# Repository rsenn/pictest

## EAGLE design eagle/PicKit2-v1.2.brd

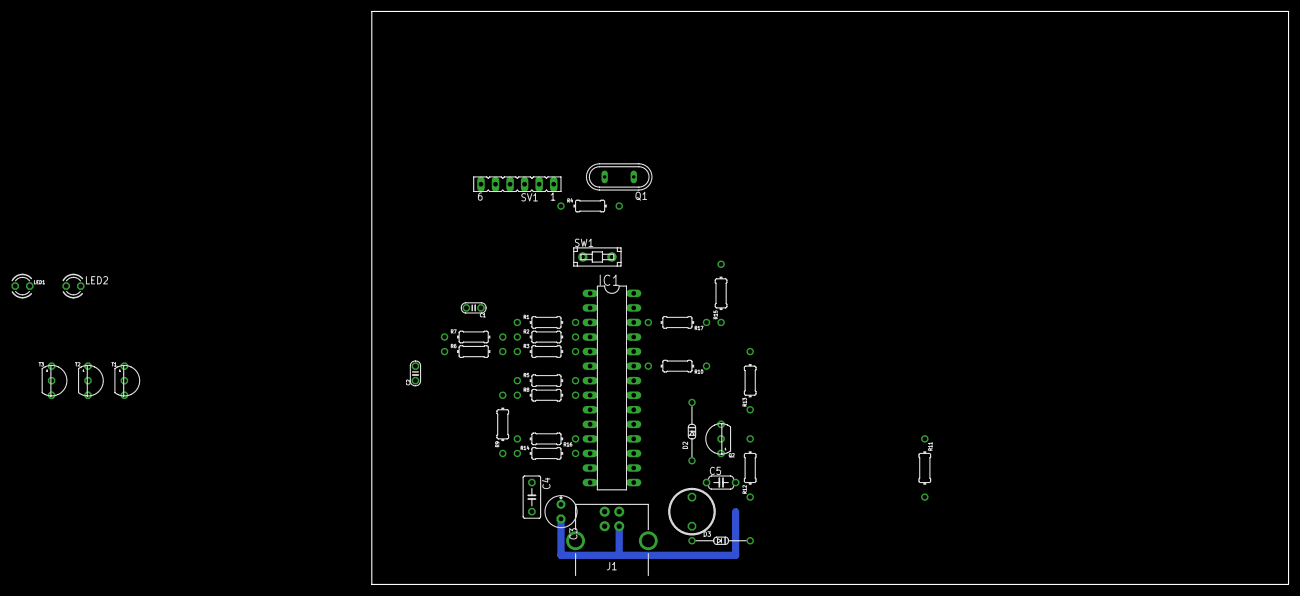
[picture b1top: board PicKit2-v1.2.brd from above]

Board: 2 copper layers, 160.0 x 100.0 mm, 36 parts (0 on the bottom side), 32 nets.

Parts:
C1, C2: 22p; C025-020X036
C3: 47 μF; E2,5-6E
C4: 0.47 μF; C050-030X075
C5: 0.1 μF; C050-024X044
D2: 1N5817-B; DO34Z10
D3: DO34-10
IC1: PIC18F2550_28DIP; DIL28-3
J1: USB-PRINT; USB-B-PRINT
L1: 680μH; L-8R
LED1: Red Busy; LED_3MM
LED2: Green Power; LED3MM
Q1: 20 MHz; QS
Q2: 2N3906; TO92
R1, R6, R7, R9: 4.7kΩ; 0204/10
R2, R3, R4, R13: 100Ω; 0204/10
R5, R10, R11: 10kΩ; 0204/10
R8: 2.7kΩ; 0204/10
R12: 100kΩ; 0204/10
R14: 1kΩ; 0204/10
R15, R16: 330Ω; 0204/10
R17: 22kΩ; 0204/10
SV1: FE06
SW1: PB-1P-1T; PB-1P1T
T1, T2, T3: 2N3904; TO92

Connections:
GND: C1.2, C2.2, C3.-, C4.2, C5.2, IC1.8, IC1.19, J1.GND, LED1.K, LED2.K, R6.1, R7.1, R8.2, SV1.3, SW1.2, T1.1, T2.1, T3.1
unnamed: C1.1, IC1.9, Q1.1
unnamed: C2.1, IC1.10, Q1.2
unnamed: IC1.3, R1.2
unnamed: IC1.4, R2.2
unnamed: IC1.5, R3.2
unnamed: IC1.6, R4.2
unnamed: IC1.7, R5.2
unnamed: D2.C, R1.1, SV1.2
unnamed: R2.1, R7.2, SV1.4
unnamed: R3.1, R6.2, SV1.5
unnamed: R4.1, SV1.6
unnamed: IC1.2, R8.1, R9.2
unnamed: IC1.23, R10.2
unnamed: R10.1, T1.2
unnamed: R11.2, T1.3
unnamed: Q2.2, R11.1, R12.2
unnamed: C3.+, D3.C, Q2.1, R9.1, R12.1
unnamed: IC1.12, R14.2
unnamed: R5.1, T2.2
unnamed: Q2.3, R13.1, SV1.1
unnamed: R13.2, T2.3
unnamed: R14.1, T3.2
unnamed: D3.A, L1.P$1, T3.3
unnamed: LED2.A, R15.2
unnamed: IC1.11, R16.1
unnamed: LED1.A, R16.2
unnamed: IC1.16, J1.D-
unnamed: IC1.15, J1.D+
unnamed: IC1.26, R17.2, SW1.1
VDD: C5.1, D2.A, IC1.20, J1.VBUS, L1.P$2, R15.1, R17.1
VUSB: C4.1, IC1.14

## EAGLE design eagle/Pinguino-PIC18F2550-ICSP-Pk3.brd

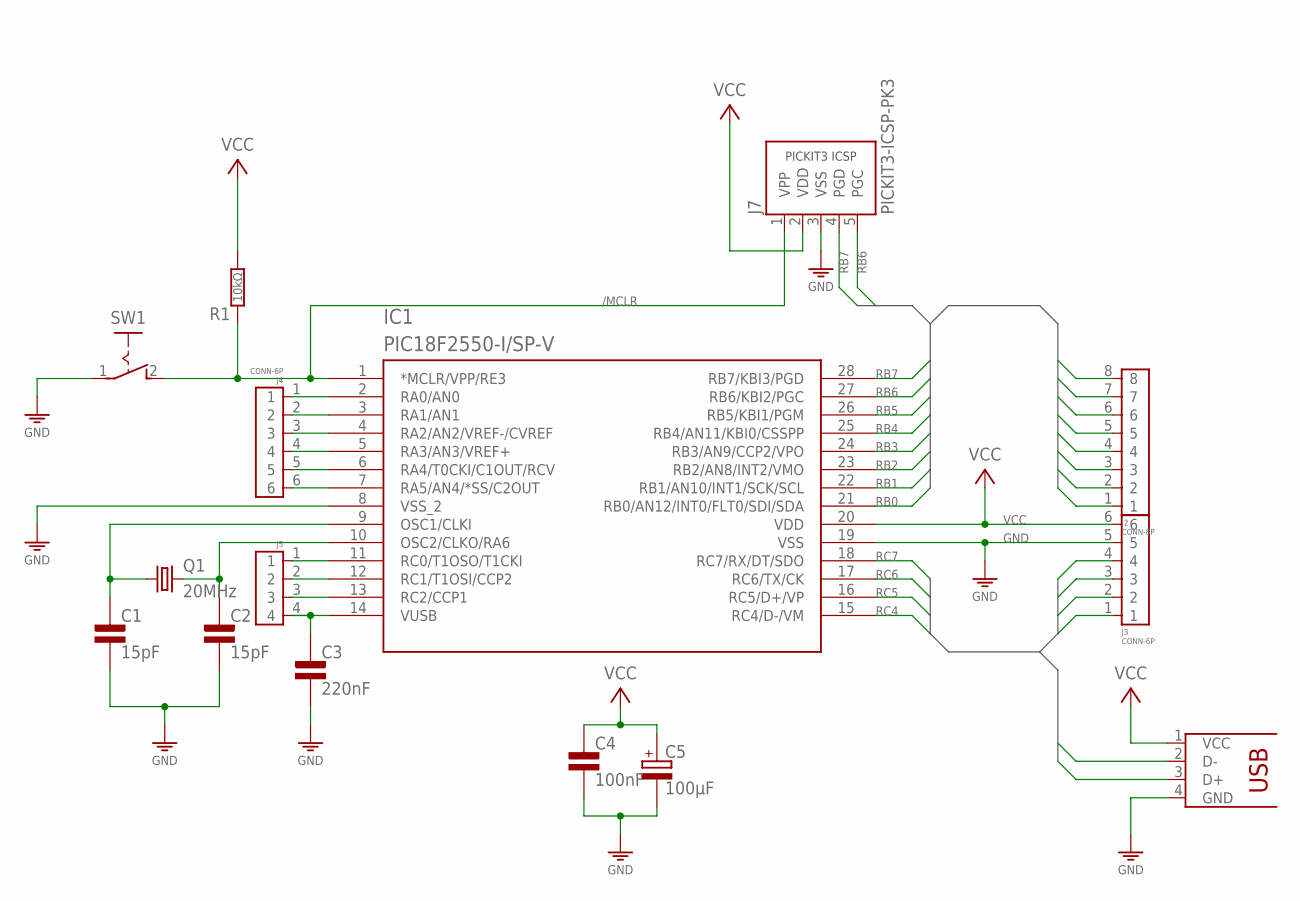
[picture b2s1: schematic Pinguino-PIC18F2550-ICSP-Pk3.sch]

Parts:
C1, C2: 15pF; C025-015X024
C3: 220nF; C075-032X103
C4: 100nF; C025-015X024
C5: 100μF; E2,5-4
IC1: PIC18F2550-I/SP-V; DIL28-3/V
J1: USB-PRINT; USB-B-PRINT
J2: CONN-8P
J3, J4: CONN-6P
J5: CONN-4P-4P; CONN-4P
J7: PICKIT3-ICSP-PK3; PIC-PK3
J8: VCC_GNDPWR-R; PWR-R
Q1: 20MHz; HC49
R1: 10kΩ; 0204/10
SW1: PB-1P-1T; PB-1P1T

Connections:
/MCLR: IC1.1 (*MCLR/VPP/RE3), J7.1 (VPP), R1.2, SW1.2 (S)
GND: C1.2, C2.2, C3.2, C4.2, C5.-, IC1.8 (VSS_2), IC1.19 (VSS), J1.4 (GND), J3.5, J7.3 (VSS), J8.1 (GND), SW1.1
unnamed: C2.1, IC1.10 (OSC2/CLKO/RA6), Q1.2
unnamed: C1.1, IC1.9 (OSC1/CLKI), Q1.1
unnamed: C3.1, IC1.14 (VUSB), J5.4
unnamed: IC1.3 (RA1/AN1), J4.2
unnamed: IC1.2 (RA0/AN0), J4.1
unnamed: IC1.4 (RA2/AN2/VREF-/CVREF), J4.3
unnamed: IC1.5 (RA3/AN3/VREF+), J4.4
unnamed: IC1.6 (RA4/T0CKI/C1OUT/RCV), J4.5
unnamed: IC1.7 (RA5/AN4/*SS/C2OUT), J4.6
unnamed: IC1.12 (RC1/T1OSI/CCP2), J5.2
unnamed: IC1.11 (RC0/T1OSO/T1CKI), J5.1
unnamed: IC1.13 (RC2/CCP1), J5.3
RB0: IC1.21 (RB0/AN12/INT0/FLT0/SDI/SDA), J2.1
RB1: IC1.22 (RB1/AN10/INT1/SCK/SCL), J2.2
RB2: IC1.23 (RB2/AN8/INT2/VMO), J2.3
RB3: IC1.24 (RB3/AN9/CCP2/VPO), J2.4
RB4: IC1.25 (RB4/AN11/KBI0/CSSPP), J2.5
RB5: IC1.26 (RB5/KBI1/PGM), J2.6
RB6: IC1.27 (RB6/KBI2/PGC), J2.7, J7.5 (PGC)
RB7: IC1.28 (RB7/KBI3/PGD), J2.8, J7.4 (PGD)
RC4: IC1.15 (RC4/D-/VM), J1.3 (D+), J3.1
RC5: IC1.16 (RC5/D+/VP), J1.2 (D-), J3.2
RC6: IC1.17 (RC6/TX/CK), J3.3
RC7: IC1.18 (RC7/RX/DT/SDO), J3.4
VCC: C4.1, C5.+, IC1.20 (VDD), J1.1 (VCC), J3.6, J7.2 (VDD), J8.2 (VCC), R1.1

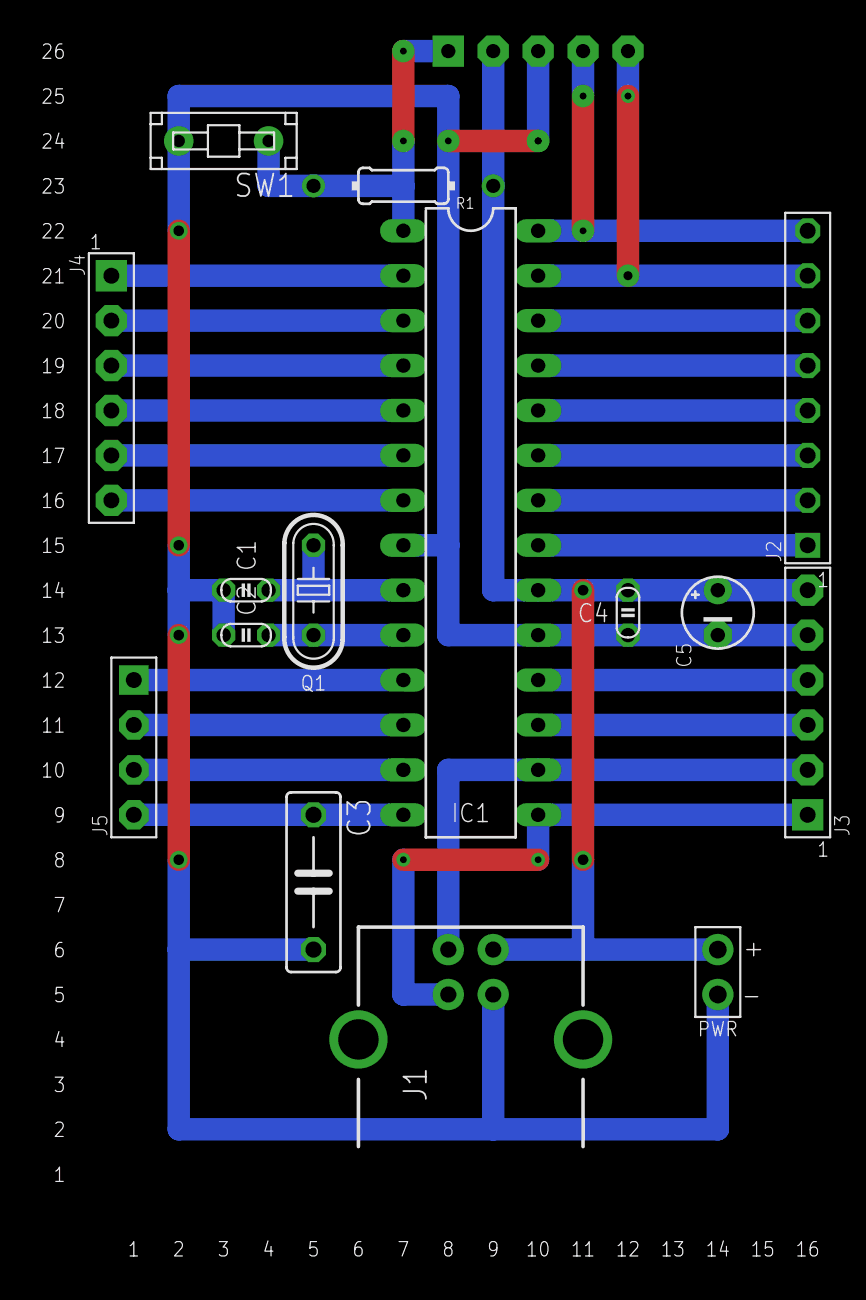
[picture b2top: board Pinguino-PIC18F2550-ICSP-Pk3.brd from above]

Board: 2 copper layers, 16 parts (0 on the bottom side), 27 nets.

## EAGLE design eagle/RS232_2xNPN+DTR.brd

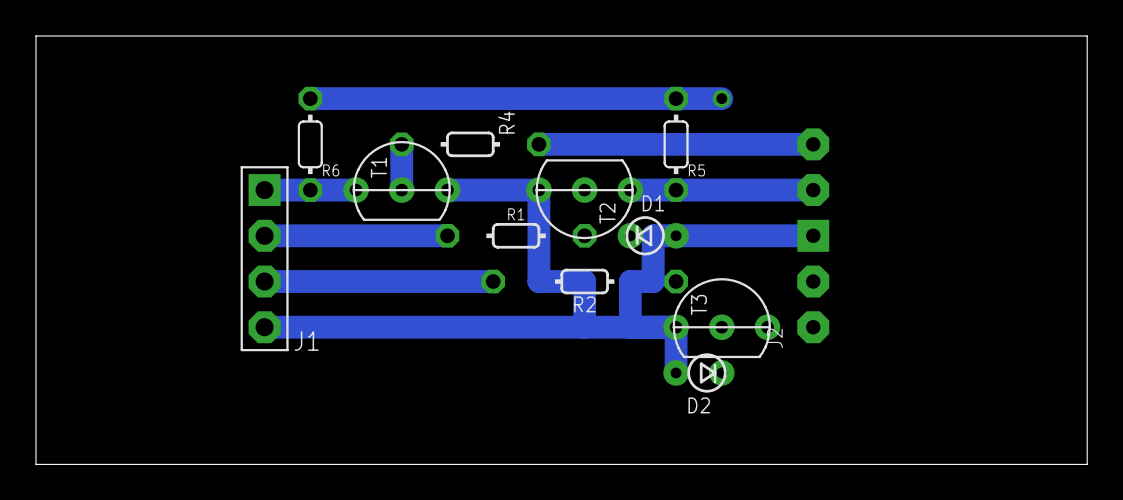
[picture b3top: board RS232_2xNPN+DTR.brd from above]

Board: 2 copper layers, 58.4 x 23.8 mm, 12 parts (0 on the bottom side), 11 nets.

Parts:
D1, D2: 1N4148; DO34-2,5-A
J1: COMPORT-4PIN-NEW-L; RS232-4PIN-NEW-L
J2: PIC-UART-MCLR
R1: 10kΩ; 0202/7
R2: 10kΩ; 0202/10
R4: 4.7kΩ; 0202/7-V
R5, R6: 1kΩ; 0202/5-V
T1, T2: BC547; TO92-CBE
T3: BC557; TO92-CBE

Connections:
GND: D1.A, D2.A, J1.4, J2.19, T1.E, T2.E, T3.C
unnamed: J2.18, R5.1, T2.C
unnamed: D1.C, R1.1, T2.B
unnamed: J1.2, R1.2
unnamed: J2.17, R4.1
unnamed: R4.2, T1.B
unnamed: D2.C, R2.1, T3.B
unnamed: J1.3, R2.2
unnamed: J2.1, T3.E
unnamed: J1.1, R6.1, T1.C
VDD: J2.20, R5.2, R6.2

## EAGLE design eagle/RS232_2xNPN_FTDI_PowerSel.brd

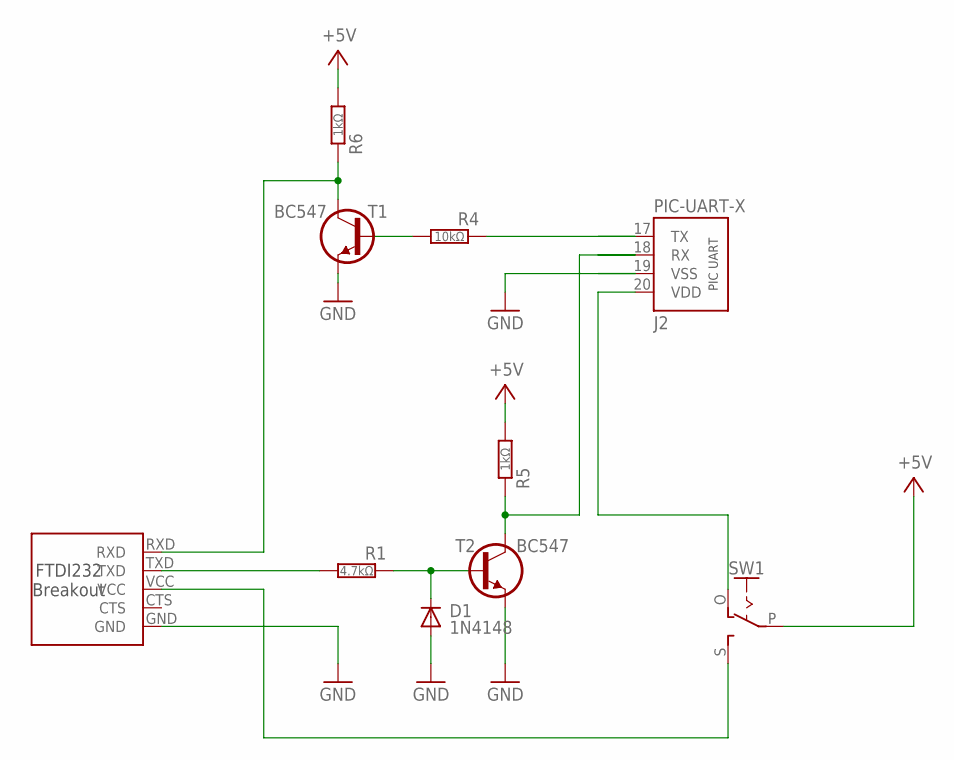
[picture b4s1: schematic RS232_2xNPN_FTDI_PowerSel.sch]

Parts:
D1: 1N4148; DO34-5V
J1: FTDI232-BO-5P-L; FTDI232-BO-5-L
J2: PIC-UART-X
R1: 4.7kΩ; 0202/7
R4: 10kΩ; 0202/7
R5: 1kΩ; 0202/7-V
R6: 1kΩ; 0202/7
SW1: SL-SW-1P-2T-JPSW; JPSW-1P2T
T1, T2: BC547; TO92-CBE

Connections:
+5V: R5.2, R6.2, SW1.P
GND: D1.A, J1.GND, J2.19 (VSS), T1.E, T2.E
unnamed: J2.18 (RX), R5.1, T2.C
unnamed: D1.C, R1.1, T2.B
unnamed: J1.TXD, R1.2
unnamed: J2.17 (TX), R4.1
unnamed: R4.2, T1.B
unnamed: J2.20 (VDD), SW1.O
unnamed: J1.VCC, SW1.S
unnamed: J1.RXD, R6.1, T1.C

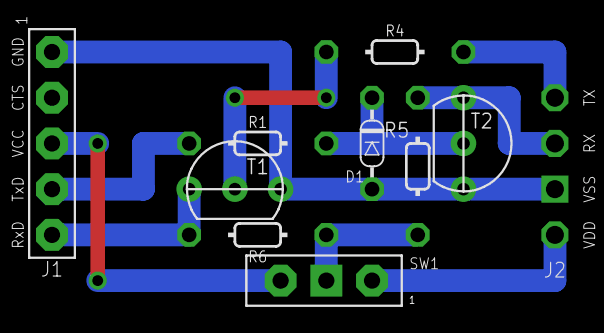
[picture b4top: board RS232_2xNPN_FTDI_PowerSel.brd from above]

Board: 2 copper layers, 10 parts (0 on the bottom side), 10 nets.
